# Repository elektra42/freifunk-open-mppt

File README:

These are preliminary sources and CAD files from the
Freifunk-Open-MPP-Tracker project.

SOME LICENSE-FOO:
+++++++++++++++++ 

This is a Open-Source and Open-Hardware project under General Public License
v2 and Creative Commons - Attribution - ShareAlike 3.0 

For more information, check out the LICENSE file.

A quick overview of the subdirectories:
+++++++++++++++++++++++++++++++++++++++

AVR-FUSES
+++++++++

Contains a XML configuration file to program the fuses of the AVR. I am
using the AVR dragon board and AVR-Burn-O-Mat software to program the fuses.

SCHEMATIC AND BOARD
+++++++++++++++++++

ECAD files and component libraries, made with KiCAD. KiCAD is a free and
open ECAD tool.  Due to the intend to provide a open hardware and open
software project for DIY home-brewers, I have decided to use a free and open
source ECAD software tool, too. It is my first project with KiCAD, though.

uC-SOURCECODE
+++++++++++++

AVR-GCC source and Makefile. 

SOME NOTES ABOUT THIS DESIGN
++++++++++++++++++++++++++++

Basically this hardware has two building blocks: 

The MPP controller section and the buck converter.

At the moment, the buck converter section is based on the el cheapo and
low-fi MC33063 controller chip.  It can easily be replaced by a faster and
more fancy switch converter IC to construct a more powerful and slightly more 
efficient buck converter section.  However, with the external powerful P-MOS
switches, the efficiency was already around 94% with the first prototype 
(measured at 2 Ampere output current).

One reason to replace the MC33063 might be noise. Under low load, the
MC33063 will skip pulses of the PWM, so the switching frequency becomes
audible.

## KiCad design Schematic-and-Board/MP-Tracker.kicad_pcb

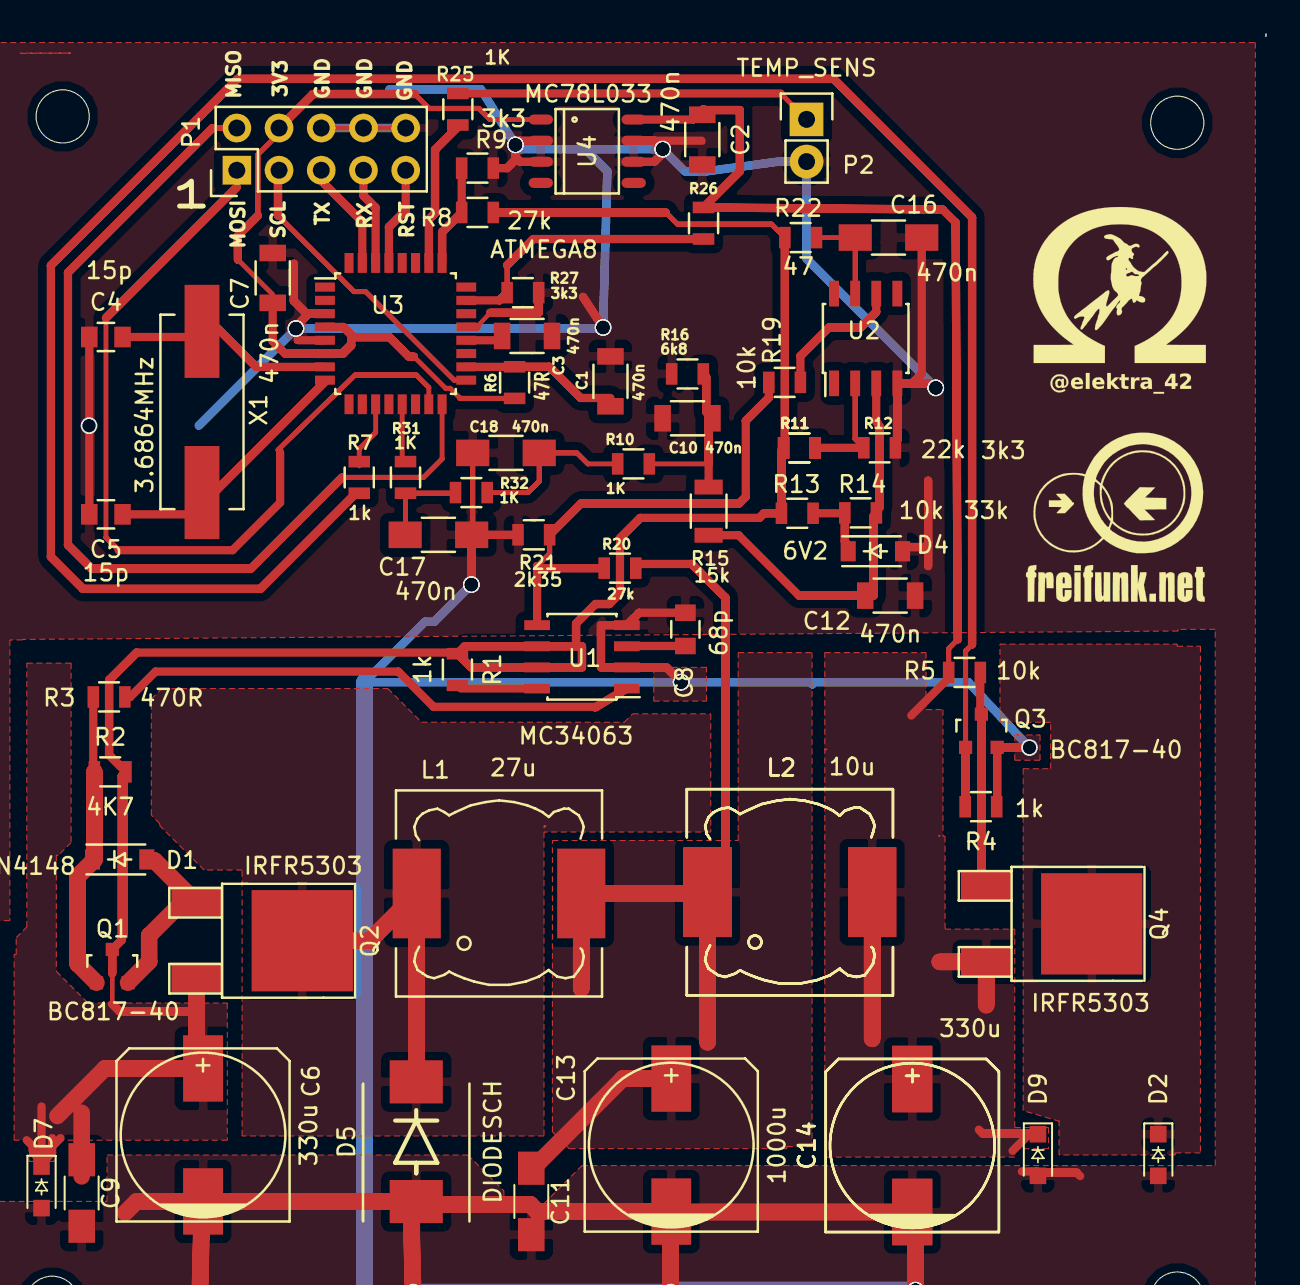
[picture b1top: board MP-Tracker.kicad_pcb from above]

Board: 2 copper layers, 64 parts (0 on the bottom side), 39 nets.

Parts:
C1, C2, C3, C7, C10, C12: 470n; C_1206
C4, C5: 15p; C_0805
C6, C14: 330u; c_elec_10x10
C8: 68p; C_0805
C9, C11: 100n; C_1206_HandSoldering
C13: 1000u; c_elec_10x10
C14#2: c_elec_10x10
C16, C17, C18: 470n; C_1206_HandSoldering
D1: 1N4148; SOD-123
D2, D7, D9: 1N4001; D_SOD-323_HandSoldering
D4: 6V2; SOD-123
D5: DIODESCH; DO-214AB
L1: 27u; Choke_SMD_12x12mm_h8mm
L2: Choke_SMD_12x12mm_h8mm
L2#2: 10u; Choke_SMD_12x12mm_h8mm
P1: Pin_Header_Straight_2x05
P2: TEMP_SENS; Pin_Header_Straight_1x02
Q1, Q3: BC817-40; SOT-23
Q2, Q4: IRFR5303; TO-252-2Lead
R1, R4, R7: 1k; R_0805
R2: 4K7; R_0805
R3: 470R; R_0805
R5, R13, R19: 10k; R_0805
R6: 47R; R_0805
R8, R20: 27k; R_0805
R9, R12, R27: 3k3; R_0805
R10, R25, R31, R32: 1K; R_0805
R11, R11#2: 22k; R_0805
R14: 33k; R_0805
R15: 15k; R_1206
R16: 6k8; R_0805
R21: 2k35; R_0805
R22: 47; R_0805
R26: 15k; R_0805
U1: MC34063; SOIC-8_3.9x4.9mm_Pitch1.27mm
U2: TL081; SOIC-8-1EP_3.9x4.9mm_Pitch1.27mm
U3: ATMEGA8; LQFP-32_7x7mm_Pitch0.8mm
U4: MC78L033; SO-8
X1: 3.6864MHz; Crystal_HC49-SD_SMD

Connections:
+3.3V: C7.1, P1.4, R6.1, U3.4, U3.6, U4.1
+BATT: C2.1, C14.1, C14#2.1, D9.1, L2.2, L2#2.2, Q4.3, R5.1, R26.1, U4.8
GNDPWR: C1.2, C2.2, C3.2, C4.1, C5.2, C6.2, C7.2, C8.2, C9.2, C10.2, C11.2, C12.2, C13.2, C14.2, C14#2.2, C16.2, C17.2, C18.2, D2.2, D4.2, D5.1, D7.2, D9.2, P1.6, P1.8, P1.10, P2.2, Q3.2, R4.1, R9.2, R12.2, R16.2, R21.2, R27.2, U1.2, U1.4, U2.4, U3.3, U3.5, U3.21, U4.2, U4.3, U4.6, U4.7
unnamed: C1.1, R6.2, U3.18
unnamed: C3.1, U3.20
unnamed: C4.2, U3.7, X1.1
unnamed: C5.1, U3.8, X1.2
unnamed: C8.1, U1.3
unnamed: C10.1, R10.2, R15.1, R16.1
unnamed: C11.1, C13.1, L1.2, L2.1, L2#2.1, R20.1
unnamed: C12.1, R14.1, R15.2, U2.3
unnamed: C16.1, R22.2, U2.7
unnamed: C17.1, R31.2, R32.1
unnamed: C18.1, R10.1, R32.2
unnamed: D1.2, Q1.2, Q2.1
unnamed: D1.1, Q1.1, R2.1, R3.1
unnamed: D4.1, R13.2, R14.2
unnamed: D5.2, L1.1, Q2.2
unnamed: P1.1, U3.15
unnamed: P1.2, U3.16
unnamed: P1.3, U3.17
unnamed: P1.5, U3.31
unnamed: P1.7, U3.30
unnamed: P1.9, U3.29
unnamed: P2.1, R25.2
unnamed: Q3.1, R4.2, R7.1
unnamed: Q3.3, Q4.1, R5.2
unnamed: R1.2, U1.8
unnamed: R3.2, U1.1
unnamed: R7.2, U3.11
unnamed: R8.2, R9.1, U3.25
unnamed: R11.2, R11#2.2, R12.1, U2.2
unnamed: R19.1, U2.6
unnamed: R19.2, R20.2, R21.1, U1.5
unnamed: R25.1, U3.26
unnamed: R26.2, R27.1, U3.23
unnamed: R31.1, U3.13
VAA: D2.1, Q4.2
VCC: C6.1, C9.1, D7.1, Q1.3, Q2.3, R1.1, R2.2, R8.1, R11.1, R11#2.1, R13.1, R22.1, U1.6, U1.7

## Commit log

2017-02-27 Initial commit of the prototype files
2017-02-27 Modified README file.
2017-02-27 Modified README
2017-02-27 Minor README.md changes.
2017-02-27 Added a PDF of the schematic.
2017-03-01 Switched to interrupt based sleep (idle) routine instead of delay routine to save power.
2017-04-07 New procedure for maximum power point detection (faster, simpler, more efficient).
2017-04-07 New major revision of schematic. The most notable changes: Added three 3-step R/C filters to cancel noise from uC PWM and for current measurement. Switched from TL081 to MC4558 dual-OP-amp. (Better p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
2017-05-26 Added bootloader and TL081 library
2017-05-26 Update Fuse definition for AVR-Burn-O-Mat
2017-05-26 Update schematic and board design and firmware source.
2017-05-27 Fixed reverse diode image in slide.
2017-06-07 Add slides about the project in English from Battlemesh v10
2017-06-07 Updated PDF document of the schematic.
2017-06-20 added external references
    some Markdown formatting
2017-08-29 Updated firmware with temperature sensor support (KTY81-210) Minor fixes in the schematic.
2017-08-29 Added firmware binary
2017-10-10 Improved regulating behavior at charge end, temperature controlled charge end voltage in µC firmware.

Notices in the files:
Schematic-and-Board/MP-Tracker.kicad_pcb:
Copyright 2017 Corinna 'Elektra' Aichele
License: Creative Commons - Attribution - ShareAlike 3.0
http://creativecommons.org/licenses/by-sa/3.0
